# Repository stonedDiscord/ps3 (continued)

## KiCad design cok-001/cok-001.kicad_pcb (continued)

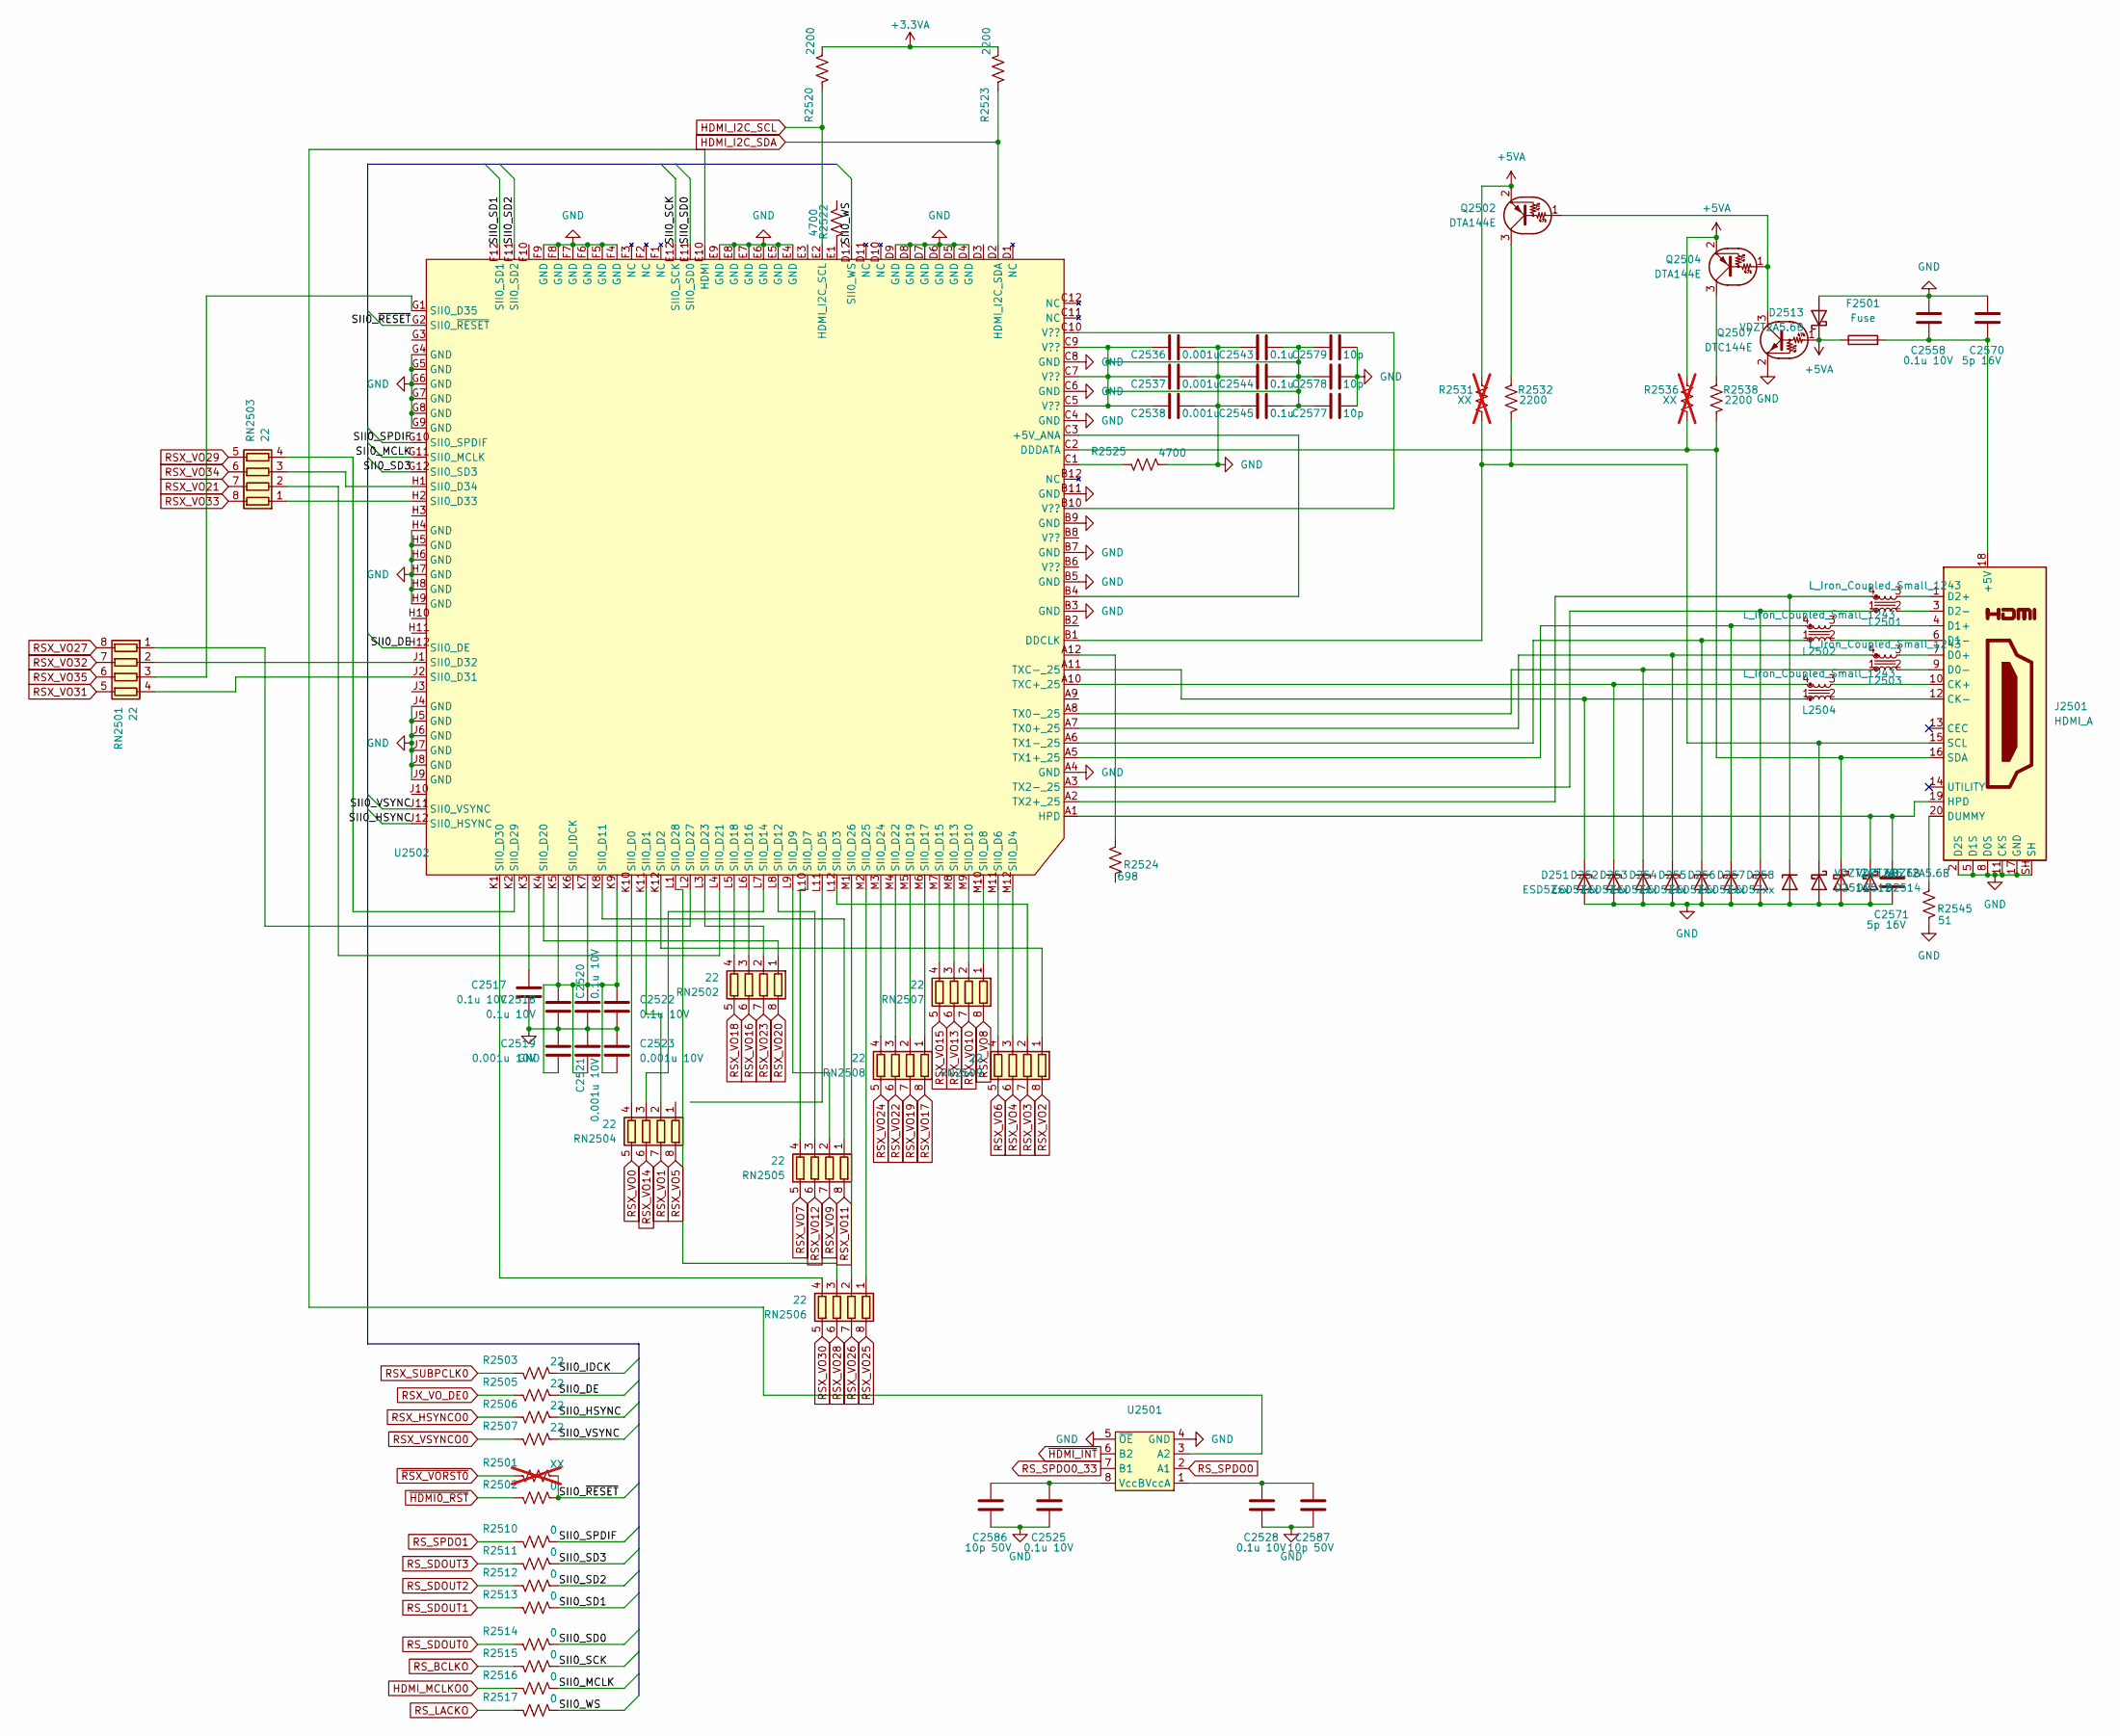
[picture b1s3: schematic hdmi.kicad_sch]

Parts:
C2517, C2518, C2520, C2522, C2525, C2528, C2558: 0.1u 10V; C_0402_1005Metric
C2519, C2521, C2523: 0.001u 10V; C_0402_1005Metric
C2536, C2537, C2538: 0.001u; C_0402_1005Metric
C2543, C2544, C2545: 0.1u; C_0402_1005Metric
C2570, C2571: 5p 16V; C_0402_1005Metric
C2577, C2578, C2579: 10p; C_0402_1005Metric
C2586, C2587: 10p 50V; C_0402_1005Metric
D251, D252, D253, D254, D255, D256, D257, D258: ESD5Zxx; D_SOD-923
D2511, D2512, D2513, D2514: VDZT2A5.6B; D_SOD-923
F2501: Fuse; Fuse_1206_3216Metric
J2501: HDMI_A; HDMI
L2501, L2502, L2503, L2504: L_Iron_Coupled_Small_1243; L_CommonModeChoke_Coilcraft_0805USB
Q2502, Q2504: DTA144E; SOT-323_SC-70
Q2507: DTC144E; SOT-323_SC-70
R2501, R2531, R2536: XX; R_0402_1005Metric; not fitted
R2502, R2510, R2511, R2512, R2513, R2514, R2515, R2516, R2517: 0; R_0402_1005Metric
R2503, R2505, R2506, R2507: 22; R_0402_1005Metric
R2520, R2523, R2532, R2538: 2200; R_0402_1005Metric
R2522, R2525: 4700; R_0402_1005Metric
R2524: 698; R_0603_1608Metric
R2545: 51; R_0402_1005Metric
RN2501, RN2502, RN2503, RN2504, RN2505, RN2506, RN2507, RN2508, RN2509: 22; R_Array_Convex_4x0402
U2501: VSSOP-8_2.3x2mm_P0.5mm
U2502: BGA-144_13.0x13.0mm_Layout12x12_P1.0mm

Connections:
+3.3VA: R2520.2, R2523.2
+5VA: D2513.1 (K), F2501.1, Q2502.2 (E), Q2504.2 (E), Q2507.1 (B), R2531.2, R2536.2
/HDMI out/SII0_DE: R2505.2, U2502.H12 (SII0_DE)
/HDMI out/SII0_HSYNC: R2506.2, U2502.J12 (SII0_HSYNC)
/HDMI out/SII0_IDCK: R2503.2
/HDMI out/SII0_MCLK: R2516.2, U2502.G11 (SII0_MCLK)
/HDMI out/SII0_SCK: R2515.2, U2502.E12 (SII0_SCK)
/HDMI out/SII0_SD0: R2514.2, U2502.E11 (SII0_SD0)
/HDMI out/SII0_SD1: R2513.2, U2502.F12 (SII0_SD1)
/HDMI out/SII0_SD2: R2512.2, U2502.F11 (SII0_SD2)
/HDMI out/SII0_SD3: R2511.2, U2502.G12 (SII0_SD3)
/HDMI out/SII0_SPDIF: R2510.2, U2502.G10 (SII0_SPDIF)
/HDMI out/SII0_VSYNC: R2507.2, U2502.J11 (SII0_VSYNC)
/HDMI out/SII0_WS: R2517.2, U2502.D12 (SII0_WS)
/HDMI out/SII0_~RESET: R2501.2, R2502.2, U2502.G2 (SII0_~RESET)
GND: C2517.2, C2518.2, C2519.1, C2520.2, C2521.1, C2522.2, C2523.1, C2525.2, C2528.2, C2536.2, C2537.2, C2538.2, C2543.1, C2544.1, C2545.1, C2558.1, C2570.1, C2571.2, C2577.2, C2578.2, C2579.2, C2586.2, C2587.2, D251.2 (A), D252.2 (A), D253.2 (A), D254.2 (A), D255.2 (A), D256.2 (A), D257.2 (A), D258.2 (A), D2511.2 (A), D2512.2 (A), D2513.2 (A), D2514.2 (A), J2501.2 (D2S), J2501.5 (D1S), J2501.8 (D0S), J2501.11 (CKS), J2501.17 (GND), J2501.SH, Q2507.2 (E), R2525.2, R2545.1, U2501.4 (GND), U2501.5 (~OE), U2502.A4 (GND), U2502.B3 (GND), U2502.B5 (GND), U2502.B7 (GND), U2502.B9 (GND), U2502.B11 (GND), U2502.C4 (GND), U2502.C6 (GND), U2502.C8 (GND), U2502.D4 (GND), U2502.D5 (GND), U2502.D6 (GND), U2502.D7 (GND), U2502.D8 (GND), U2502.D9 (GND), U2502.E4 (GND), U2502.E5 (GND), U2502.E6 (GND), U2502.E7 (GND), U2502.E8 (GND), U2502.E9 (GND), U2502.F4 (GND), U2502.F5 (GND), U2502.F6 (GND), U2502.F7 (GND), U2502.F8 (GND), U2502.F9 (GND), U2502.G4 (GND), U2502.G5 (GND), U2502.G6 (GND), U2502.G7 (GND), U2502.G8 (GND), U2502.G9 (GND), U2502.H4 (GND), U2502.H5 (GND), U2502.H6 (GND), U2502.H7 (GND), U2502.H8 (GND), U2502.H9 (GND), U2502.J4 (GND), U2502.J5 (GND), U2502.J6 (GND), U2502.J7 (GND), U2502.J8 (GND), U2502.J9 (GND); also elsewhere on the board
HDMI_I2C_SCL: R2520.1, U2502.E2 (HDMI_I2C_SCL); also elsewhere on the board
HDMI_I2C_SDA: R2523.1, U2502.D2 (HDMI_I2C_SDA); also elsewhere on the board
HDMI_MCLKO0: R2516.1; also elsewhere on the board
unnamed: C2517.1, U2502.K3
unnamed: C2518.1, C2519.2, C2520.1, C2521.2, C2522.1, C2523.2, U2502.K5, U2502.K7, U2502.K9
unnamed: C2536.1, C2537.1, C2538.1, C2543.2, C2544.2, C2545.2, C2577.1, C2578.1, C2579.1, U2502.C5 (V??), U2502.C7 (V??), U2502.C9 (V??)
unnamed: D251.1 (K), L2504.1, U2502.A11 (TXC-_25)
unnamed: D252.1 (K), L2504.4, U2502.A10 (TXC+_25)
unnamed: D253.1 (K), L2503.1, U2502.A8 (TX0-_25)
unnamed: D254.1 (K), L2503.4, U2502.A7 (TX0+_25)
unnamed: D255.1 (K), L2502.1, U2502.A6 (TX1-_25)
unnamed: D256.1 (K), L2502.4, U2502.A5 (TX1+_25)
unnamed: D257.1 (K), L2501.1, U2502.A3 (TX2-_25)
unnamed: D258.1 (K), L2501.4, U2502.A2 (TX2+_25)
unnamed: D2511.1 (K), J2501.15 (SCL), R2531.1, R2532.1, U2502.B1 (DDCLK)
unnamed: D2512.1 (K), J2501.16 (SDA), R2536.1, R2538.1, U2502.C2 (DDDATA)
unnamed: C2571.1, D2514.1 (K), J2501.19 (HPD), U2502.A1 (HPD)
unnamed: C2558.2, C2570.2, F2501.2, J2501.18 (+5V)
unnamed: J2501.10 (CK+), L2504.3
unnamed: J2501.12 (CK-), L2504.2
unnamed: J2501.7 (D0+), L2503.3
unnamed: J2501.9 (D0-), L2503.2
unnamed: J2501.4 (D1+), L2502.3
unnamed: J2501.6 (D1-), L2502.2
unnamed: J2501.1 (D2+), L2501.3
unnamed: J2501.3 (D2-), L2501.2
unnamed: J2501.20 (DUMMY), R2545.2
unnamed: Q2502.1 (B), Q2504.1 (B), Q2507.3 (C)
unnamed: Q2502.3 (C), R2532.2
unnamed: Q2504.3 (C), R2538.2
unnamed: R2522.2, U2502.E1
unnamed: R2524.2, U2502.A12
unnamed: R2525.1, U2502.C1
unnamed: RN2501.1 (R1.1), U2502.L2 (SII0_D27)
unnamed: RN2501.2 (R2.1), U2502.J1 (SII0_D32)
unnamed: RN2501.3 (R3.1), U2502.G1 (SII0_D35)
unnamed: RN2501.4 (R4.1), U2502.J2 (SII0_D31)
unnamed: RN2502.1 (R1.1), U2502.K4 (SII0_D20)
unnamed: RN2502.2 (R2.1), U2502.L3 (SII0_D23)
unnamed: RN2502.3 (R3.1), U2502.L6 (SII0_D16)
unnamed: RN2502.4 (R4.1), U2502.L5 (SII0_D18)
unnamed: RN2503.1 (R1.1), U2502.H2 (SII0_D33)
unnamed: RN2503.2 (R2.1), U2502.L4 (SII0_D21)
unnamed: RN2503.3 (R3.1), U2502.H1 (SII0_D34)
unnamed: RN2503.4 (R4.1), U2502.K2 (SII0_D29)
unnamed: RN2504.2 (R2.1), U2502.K11 (SII0_D1)
unnamed: RN2504.3 (R3.1), U2502.L7 (SII0_D14)
unnamed: RN2504.4 (R4.1), U2502.K10 (SII0_D0)
unnamed: RN2505.1 (R1.1), U2502.K8 (SII0_D11)
unnamed: RN2505.2 (R2.1), U2502.L9 (SII0_D9)
unnamed: RN2505.3 (R3.1), U2502.L8 (SII0_D12)
unnamed: RN2505.4 (R4.1), U2502.L10 (SII0_D7)
unnamed: RN2506.1 (R1.1), U2502.M2 (SII0_D25)
unnamed: RN2506.2 (R2.1), U2502.M1 (SII0_D26)
unnamed: RN2506.3 (R3.1), U2502.L1 (SII0_D28)
unnamed: RN2506.4 (R4.1), U2502.K1 (SII0_D30)
unnamed: RN2507.1 (R1.1), U2502.M10 (SII0_D8)
unnamed: RN2507.2 (R2.1), U2502.M9 (SII0_D10)
unnamed: RN2507.3 (R3.1), U2502.M8 (SII0_D13)
unnamed: RN2507.4 (R4.1), U2502.M7 (SII0_D15)
unnamed: RN2508.1 (R1.1), U2502.M6 (SII0_D17)
unnamed: RN2508.2 (R2.1), U2502.M5 (SII0_D19)
unnamed: RN2508.3 (R3.1), U2502.M4 (SII0_D22)
unnamed: RN2508.4 (R4.1), U2502.M3 (SII0_D24)
unnamed: RN2509.1 (R1.1), U2502.K12 (SII0_D2)
unnamed: RN2509.2 (R2.1), U2502.L12 (SII0_D3)
unnamed: RN2509.3 (R3.1), U2502.M12 (SII0_D4)
unnamed: RN2509.4 (R4.1), U2502.M11 (SII0_D6)
unnamed: U2501.3 (A2), U2502.E10 (HDMI)
unnamed: C2528.1, C2587.1, U2501.1 (VccA)
unnamed: C2525.1, C2586.1, U2501.8 (VccB)
unnamed: U2502.B4, U2502.C3 (+5V_ANA)
unnamed: U2502.B10 (V??), U2502.C10 (V??)
RSX_HSYNCO0: R2506.1; also elsewhere on the board
RSX_SUBPCLK0: R2503.1; also elsewhere on the board
RSX_VO0: RN2504.5 (R4.2)
RSX_VO1: RN2504.7 (R2.2)
RSX_VO2: RN2509.8 (R1.2); also elsewhere on the board
RSX_VO3: RN2509.7 (R2.2); also elsewhere on the board
RSX_VO4: RN2509.6 (R3.2); also elsewhere on the board
RSX_VO5: RN2504.8 (R1.2)
RSX_VO6: RN2509.5 (R4.2); also elsewhere on the board
RSX_VO7: RN2505.5 (R4.2)
RSX_VO8: RN2507.8 (R1.2); also elsewhere on the board
RSX_VO9: RN2505.7 (R2.2)
RSX_VO10: RN2507.7 (R2.2)
RSX_VO11: RN2505.8 (R1.2); also elsewhere on the board
RSX_VO12: RN2505.6 (R3.2)
RSX_VO13: RN2507.6 (R3.2)
RSX_VO14: RN2504.6 (R3.2)
RSX_VO15: RN2507.5 (R4.2); also elsewhere on the board
RSX_VO16: RN2502.6 (R3.2)
RSX_VO17: RN2508.8 (R1.2); also elsewhere on the board
RSX_VO18: RN2502.5 (R4.2); also elsewhere on the board
RSX_VO19: RN2508.7 (R2.2)
RSX_VO20: RN2502.8 (R1.2)
RSX_VO21: RN2503.7 (R2.2)
RSX_VO22: RN2508.6 (R3.2); also elsewhere on the board
RSX_VO23: RN2502.7 (R2.2); also elsewhere on the board
RSX_VO24: RN2508.5 (R4.2)
RSX_VO25: RN2506.8 (R1.2)
RSX_VO26: RN2506.7 (R2.2)
RSX_VO27: RN2501.8 (R1.2)
RSX_VO28: RN2506.6 (R3.2)
RSX_VO29: RN2503.5 (R4.2)
RSX_VO30: RN2506.5 (R4.2); also elsewhere on the board
RSX_VO31: RN2501.5 (R4.2)
RSX_VO32: RN2501.7 (R2.2); also elsewhere on the board
RSX_VO33: RN2503.8 (R1.2)
RSX_VO34: RN2503.6 (R3.2)
RSX_VO35: RN2501.6 (R3.2); also elsewhere on the board
RSX_VO_DE0: R2505.1
RSX_VSYNCO0: R2507.1
RS_BCLKO: R2515.1; also elsewhere on the board
RS_LACKO: R2517.1
RS_SDOUT0: R2514.1; also elsewhere on the board
RS_SDOUT1: R2513.1; also elsewhere on the board
RS_SDOUT2: R2512.1
RS_SDOUT3: R2511.1
RS_SPDO0: U2501.2 (A1)
RS_SPDO0_33: U2501.7 (B1); also elsewhere on the board
RS_SPDO1: R2510.1
~HDMI0_RST: R2502.1; also elsewhere on the board
~HDMI_INT: U2501.6 (B2)
~RSX_VORST0: R2501.1

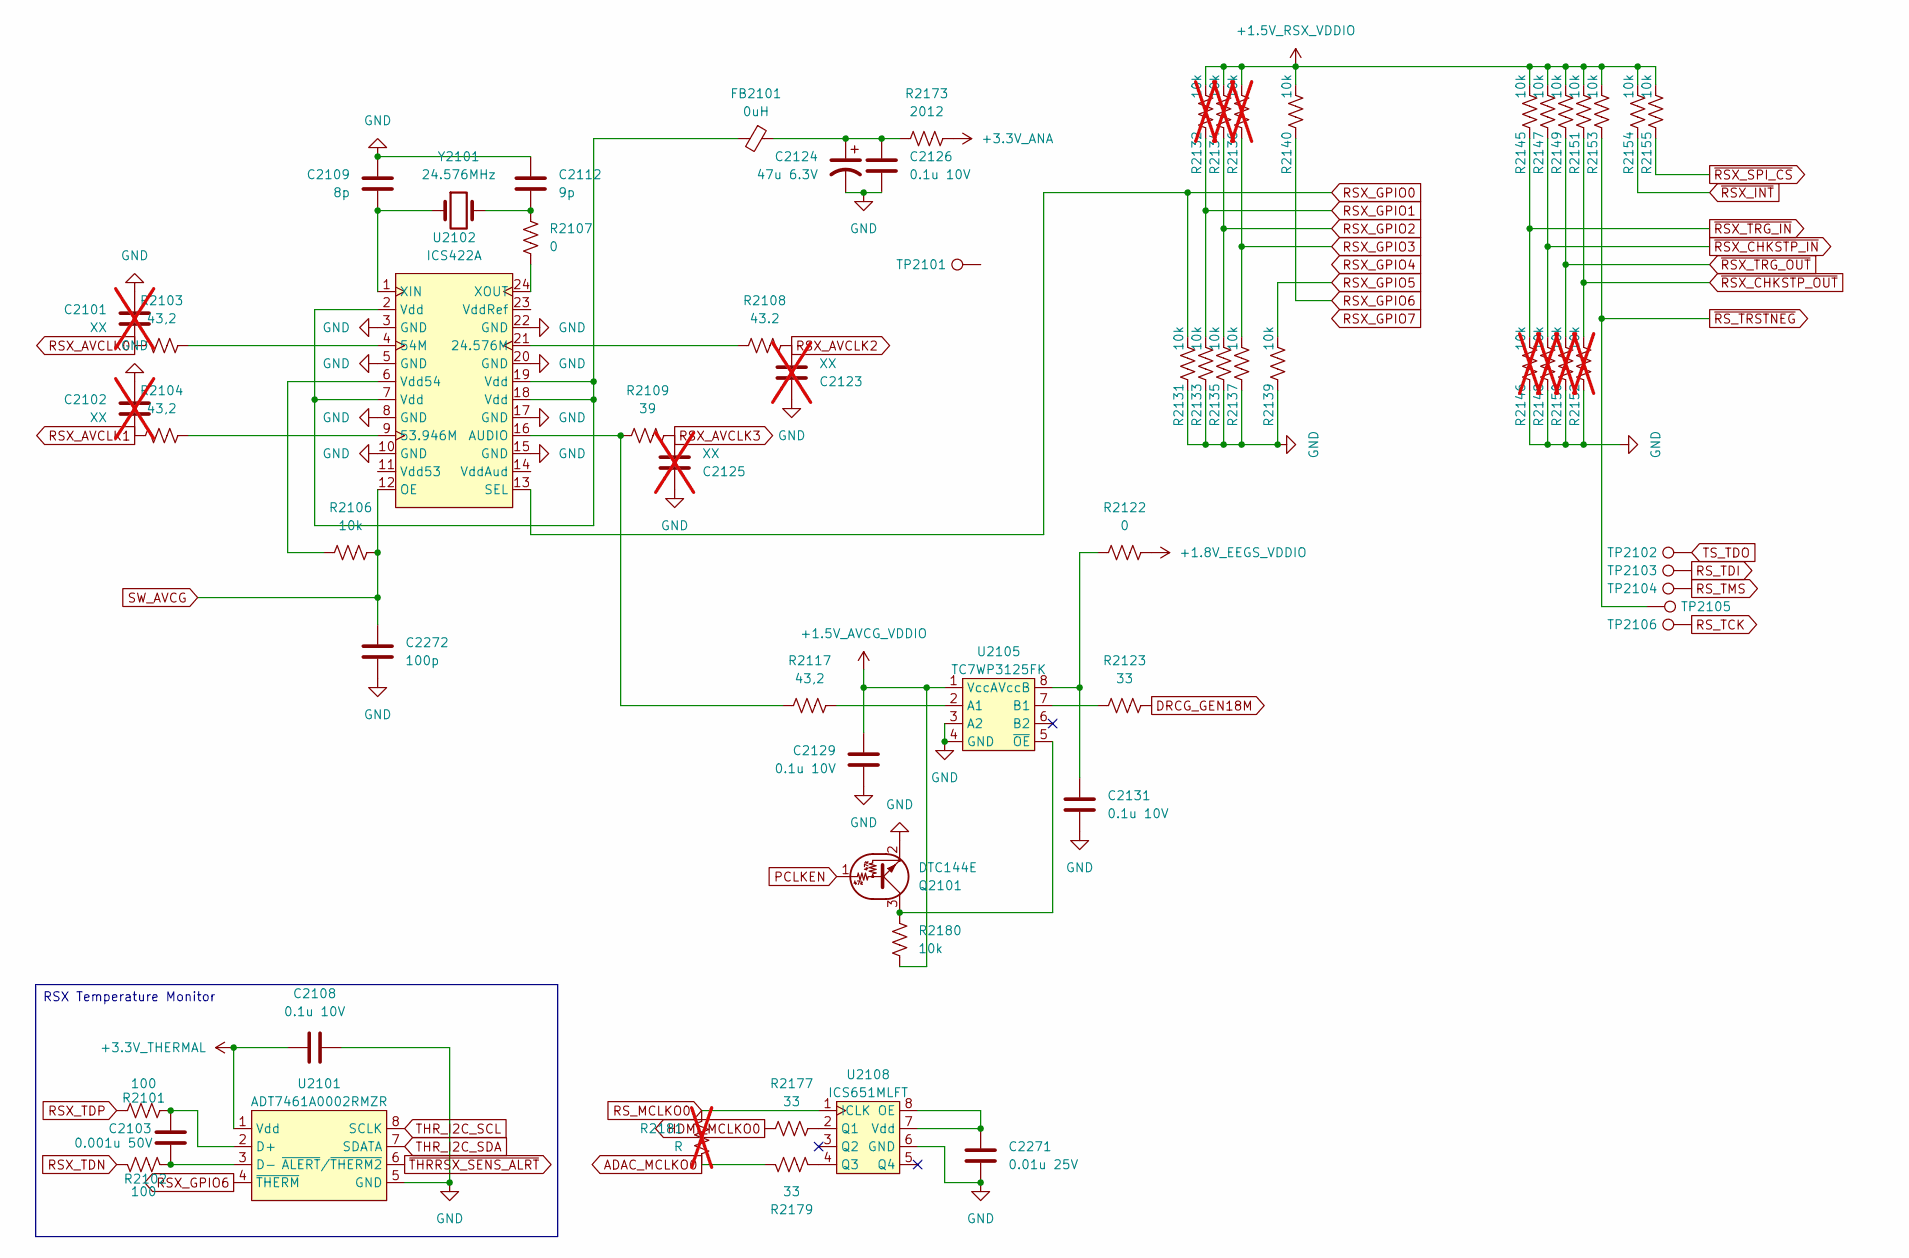
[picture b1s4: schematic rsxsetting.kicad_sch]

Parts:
C2101, C2102, C2123, C2125: XX; C_0402_1005Metric; not fitted
C2103: 0.001u 50V; C_0402_1005Metric
C2108, C2126, C2129, C2131: 0.1u 10V; C_0402_1005Metric
C2109: 8p; C_0402_1005Metric
C2112: 9p; C_0402_1005Metric
C2124: 47u 6.3V; CP_EIA-3216-10_Kemet-I
C2271: 0.01u 25V; C_0402_1005Metric
C2272: 100p; C_0402_1005Metric
FB2101: 0uH; L_0603_1608Metric
Q2101: DTC144E; SOT-323_SC-70
R2101, R2102: 100; R_0402_1005Metric
R2103, R2104, R2117: 43,2; R_0402_1005Metric
R2106, R2131, R2133, R2135, R2137, R2139, R2140, R2145, R2147, R2149, R2151, R2153, R2154, R2155, R2180: 10k; R_0402_1005Metric
R2107, R2122: 0; R_0603_1608Metric
R2108: 43.2; R_0402_1005Metric
R2109: 39; R_0402_1005Metric
R2123, R2177, R2179: 33; R_0402_1005Metric
R2132, R2134, R2136, R2146, R2148, R2150, R2152: 10k; R_0402_1005Metric; not fitted
R2173: 2012; R_0603_1608Metric
R2181: R; R_0402_1005Metric; not fitted
TP2101, TP2102, TP2103, TP2104, TP2105, TP2106: TestPoint; TestPoint_Pad_1.0x1.0mm
U2101: ADT7461A0002RMZR; MSOP-8_2.9x4mm_P0.65mm
U2102: ICS422A; SSOP-24_3.9x8.7mm_P0.635mm
U2105: TC7WP3125FK; VSSOP-8_2.3x2mm_P0.5mm
U2108: ICS651MLFT; SSOP-8_3.9x5.05mm_P1.27mm
Y2101: 24.576MHz; Crystal_SMD_5032-2Pin_5.0x3.2mm

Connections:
+1.5V_AVCG_VDDIO: C2129.1, R2180.2, U2105.1 (VccA); also elsewhere on the board
+1.5V_RSX_VDDIO: R2132.2, R2134.2, R2136.2, R2140.2, R2145.2, R2147.2, R2149.2, R2151.2, R2153.2, R2154.2, R2155.2; also elsewhere on the board
+1.8V_EEGS_VDDIO: R2122.2; also elsewhere on the board
+3.3V_ANA: R2173.2; also elsewhere on the board
+3.3V_THERMAL: C2108.1, U2101.1 (Vdd); also elsewhere on the board
ADAC_MCLKO0: R2179.1, R2181.1; also elsewhere on the board
DRCG_GEN18M: R2123.2; also elsewhere on the board
GND: C2101.1, C2102.1, C2108.2, C2109.1, C2112.1, C2123.1, C2124.2, C2125.1, C2126.2, C2129.2, C2131.2, C2271.2, C2272.2, Q2101.2 (E), R2131.1, R2133.1, R2135.1, R2137.1, R2139.1, R2146.1, R2148.1, R2150.1, R2152.1, U2101.5 (GND), U2102.3 (GND), U2102.5 (GND), U2102.8 (GND), U2102.10 (GND), U2102.15 (GND), U2102.17 (GND), U2102.20 (GND), U2102.22 (GND), U2105.3 (A2), U2105.4 (GND), U2108.6 (GND); also elsewhere on the board
HDMI_MCLKO0: R2177.1; also elsewhere on the board
unnamed: C2112.2, R2107.1, Y2101.2
unnamed: C2124.1, C2126.1, FB2101.1, R2173.1
unnamed: FB2101.2, U2102.2 (Vdd), U2102.7 (Vdd), U2102.18 (Vdd), U2102.19 (Vdd)
unnamed: Q2101.3 (C), R2180.1, U2105.5 (~OE)
unnamed: C2103.2, R2101.2, U2101.2 (D+)
unnamed: C2103.1, R2102.1, U2101.3 (D-)
unnamed: R2108.1, U2102.21 (24.576M)
unnamed: R2104.2, U2102.9 (53.946M)
unnamed: R2103.2, U2102.4 (54M)
unnamed: R2109.1, R2117.1, U2102.16 (AUDIO)
unnamed: R2106.1, U2102.6 (Vdd54)
unnamed: C2109.2, U2102.1 (XIN), Y2101.1
unnamed: R2107.2, U2102.24 (XOUT)
unnamed: R2117.2, U2105.2 (A1)
unnamed: R2123.1, U2105.7 (B1)
unnamed: C2131.1, R2122.1, U2105.8 (VccB)
unnamed: C2271.1, U2108.7 (Vdd), U2108.8 (OE)
unnamed: R2177.2, U2108.2 (Q1)
unnamed: R2179.2, U2108.4 (Q3)
PCLKEN: Q2101.1 (B); also elsewhere on the board
RSX_AVCLK0: C2101.2, R2103.1; also elsewhere on the board
RSX_AVCLK1: C2102.2, R2104.1; also elsewhere on the board
RSX_AVCLK2: C2123.2, R2108.2; also elsewhere on the board
RSX_AVCLK3: C2125.2, R2109.2; also elsewhere on the board
RSX_GPIO0: R2131.2, U2102.13 (SEL); also elsewhere on the board
RSX_GPIO1: R2132.1, R2133.2; also elsewhere on the board
RSX_GPIO2: R2134.1, R2135.2; also elsewhere on the board
RSX_GPIO3: R2136.1, R2137.2; also elsewhere on the board
RSX_GPIO5: R2139.2; also elsewhere on the board
RSX_GPIO6: R2140.1, U2101.4 (~THERM); also elsewhere on the board
RSX_TDN: R2102.2
RSX_TDP: R2101.1
RS_MCLKO0: R2181.2, U2108.1 (ICLK)
RS_TCK: TP2106.1 (1_1); also elsewhere on the board
RS_TDI: TP2103.1 (1_1); also elsewhere on the board
RS_TMS: TP2104.1 (1_1); also elsewhere on the board
SW_AVCG: C2272.1, R2106.2, U2102.12 (OE); also elsewhere on the board
THR_I2C_SCL: U2101.8 (SCLK); also elsewhere on the board
THR_I2C_SDA: U2101.7 (SDATA); also elsewhere on the board
TS_TDO: TP2102.1 (1_1); also elsewhere on the board
~RSX_CHKSTP_IN: R2147.1, R2148.2
~RSX_CHKSTP_OUT: R2151.1, R2152.2
~RSX_INT: R2154.1; also elsewhere on the board
~RSX_SPI_CS: R2155.1; also elsewhere on the board
~RSX_TRG_IN: R2145.1, R2146.2; also elsewhere on the board
~RSX_TRG_OUT: R2149.1, R2150.2; also elsewhere on the board
~RS_TRSTNEG: R2153.1, TP2105.1 (1_1); also elsewhere on the board
~THRRSX_SENS_ALRT: U2101.6 (~ALERT/~THERM2); also elsewhere on the board

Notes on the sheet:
RSX Temperature Monitor

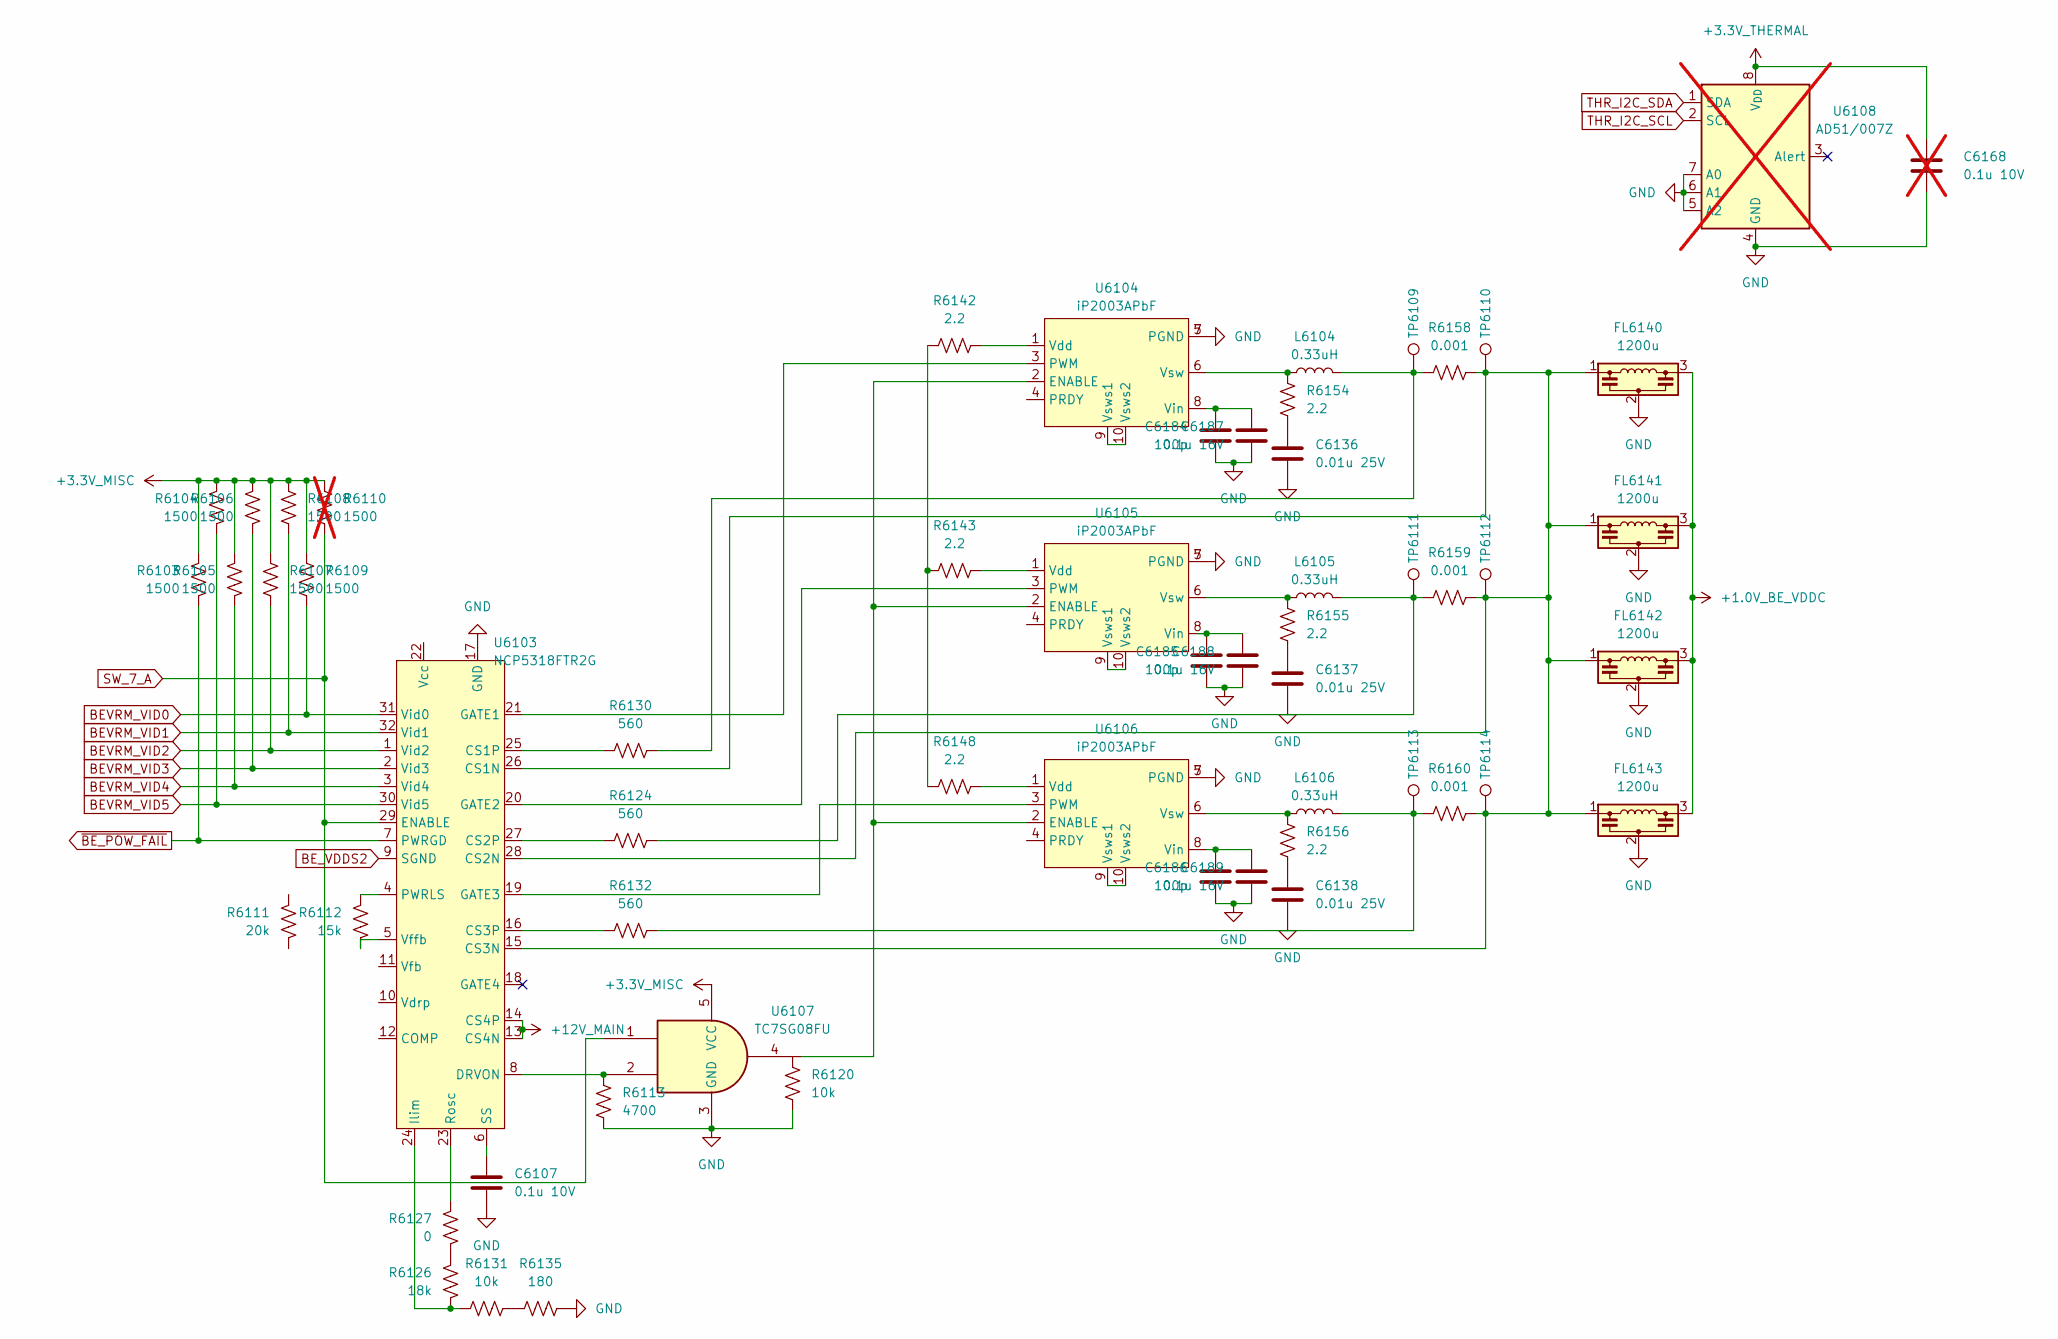
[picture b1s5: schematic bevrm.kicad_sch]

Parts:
C6107: 0.1u 10V; C_0402_1005Metric
C6136, C6137, C6138: 0.01u 25V; C_0402_1005Metric
C6168: 0.1u 10V; C_0402_1005Metric; not fitted
C6184, C6185, C6186: 100p; C_0402_1005Metric
C6187, C6188, C6189: 0.1u 16V; C_0402_1005Metric
FL6140, FL6141, FL6142, FL6143: 1200u; Proadlizer
L6104, L6105, L6106: 0.33uH; L_1212
R6103, R6104, R6105, R6106, R6107, R6108, R6109: 1500; R_0402_1005Metric
R6110: 1500; R_0402_1005Metric; not fitted
R6111: 20k; R_0402_1005Metric
R6112: 15k; R_0402_1005Metric
R6113: 4700; R_0402_1005Metric
R6120, R6131: 10k; R_0402_1005Metric
R6124, R6130, R6132: 560; R_0402_1005Metric
R6126: 18k; R_0402_1005Metric
R6127: 0; R_0402_1005Metric
R6135: 180; R_0402_1005Metric
R6142, R6143, R6148: 2.2; R_0402_1005Metric
R6154, R6155, R6156: 2.2; R_0805_2012Metric
R6158, R6159, R6160: 0.001; R_2512_6332Metric
TP6109, TP6110, TP6111, TP6112, TP6113, TP6114: TestPoint; TestPoint_Pad_D1.5mm
U6103: NCP5318FTR2G; LQFP-32_7x7mm_P0.8mm
U6104, U6105, U6106: iP2003APbF
U6107: TC7SG08FU; Texas_R-PDSO-N5_DRL-5
U6108: AD51/007Z; MSOP-8_2.9x4mm_P0.65mm; not fitted

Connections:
+1.0V_BE_VDDC: FL6140.3, FL6141.3, FL6142.3, FL6143.3; also elsewhere on the board
+3.3V_MISC: R6103.2, R6104.2, R6105.2, R6106.2, R6107.2, R6108.2, R6109.2, R6110.2, U6107.5 (VCC); also elsewhere on the board
+3.3V_THERMAL: C6168.1, U6108.8 (V_{DD}); also elsewhere on the board
+12V_MAIN: U6103.13 (CS4N), U6103.14 (CS4P); also elsewhere on the board
BEVRM_VID0: R6109.1, U6103.31 (Vid0); also elsewhere on the board
BEVRM_VID1: R6108.1, U6103.32 (Vid1); also elsewhere on the board
BEVRM_VID2: R6107.1, U6103.1 (Vid2); also elsewhere on the board
BEVRM_VID3: R6106.1, U6103.2 (Vid3); also elsewhere on the board
BEVRM_VID4: R6105.1, U6103.3 (Vid4); also elsewhere on the board
BEVRM_VID5: R6104.1, U6103.30 (Vid5); also elsewhere on the board
BE_VDDS2: U6103.9 (SGND); also elsewhere on the board
GND: C6107.1, C6136.1, C6137.1, C6138.1, C6168.2, C6184.1, C6185.1, C6186.1, C6187.1, C6188.1, C6189.1, FL6140.2, FL6141.2, FL6142.2, FL6143.2, R6113.1, R6120.1, R6135.2, U6103.17 (GND), U6104.5 (PGND), U6104.7 (PGND), U6105.5 (PGND), U6105.7 (PGND), U6106.5 (PGND), U6106.7 (PGND), U6107.3 (GND), U6108.4 (GND), U6108.5 (A2), U6108.6 (A1), U6108.7 (A0); also elsewhere on the board
unnamed: C6136.2, R6154.1
unnamed: C6137.2, R6155.1
unnamed: C6138.2, R6156.1
unnamed: L6104.1, R6130.2, R6158.1, TP6109.1 (1_1)
unnamed: L6105.1, R6124.2, R6159.1, TP6111.1 (1_1)
unnamed: L6106.1, R6132.2, R6160.1, TP6113.1 (1_1)
unnamed: R6126.2, R6127.1
unnamed: R6131.2, R6135.1
unnamed: R6142.1, R6143.1, R6148.1
unnamed: FL6140.1, FL6141.1, FL6142.1, FL6143.1, R6158.2, R6159.2, R6160.2, TP6110.1 (1_1), TP6112.1 (1_1), TP6114.1 (1_1), U6103.15 (CS3N), U6103.26 (CS1N), U6103.28 (CS2N)
unnamed: R6130.1, U6103.25 (CS1P)
unnamed: R6124.1, U6103.27 (CS2P)
unnamed: R6132.1, U6103.16 (CS3P)
unnamed: R6113.2, U6103.8 (DRVON), U6107.2
unnamed: U6103.21 (GATE1), U6104.3 (PWM)
unnamed: U6103.20 (GATE2), U6105.3 (PWM)
unnamed: U6103.19 (GATE3), U6106.3 (PWM)
unnamed: R6126.1, R6131.1, U6103.24 (Ilim)
unnamed: R6112.2, U6103.4 (PWRLS)
unnamed: R6127.2, U6103.23 (Rosc)
unnamed: C6107.2, U6103.6 (SS)
unnamed: R6112.1, U6103.5 (Vffb)
unnamed: U6104.2 (ENABLE), U6105.2 (ENABLE), U6106.2 (ENABLE), U6107.4
unnamed: R6142.2, U6104.1 (Vdd)
unnamed: C6184.2, C6187.2, U6104.8 (Vin)
unnamed: L6104.2, R6154.2, U6104.6 (Vsw)
unnamed: U6104.9 (Vsws1), U6104.10 (Vsws2)
unnamed: R6143.2, U6105.1 (Vdd)
unnamed: C6185.2, C6188.2, U6105.8 (Vin)
unnamed: L6105.2, R6155.2, U6105.6 (Vsw)
unnamed: U6105.9 (Vsws1), U6105.10 (Vsws2)
unnamed: R6148.2, U6106.1 (Vdd)
unnamed: C6186.2, C6189.2, U6106.8 (Vin)
unnamed: L6106.2, R6156.2, U6106.6 (Vsw)
unnamed: U6106.9 (Vsws1), U6106.10 (Vsws2)
SW_7_A: R6110.1, U6103.29 (ENABLE), U6107.1; also elsewhere on the board
THR_I2C_SCL: U6108.2 (SCL); also elsewhere on the board
THR_I2C_SDA: U6108.1 (SDA); also elsewhere on the board
~BE_POW_FAIL: R6103.1, U6103.7 (PWRGD); also elsewhere on the board
